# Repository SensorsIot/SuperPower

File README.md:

# SuperPower
Here you should find the best power supplies for your low-power projects. Because of different requirements for an Raspberry Pi and micro-controllers like the ESP32 we split the project into two boards, one for the Raspberry Pi (SuperPower-Rpi) and one for micro-controllers (SuperPower-uC) with low power.

##### [SuperPower-Rpi](/SuperPower-RPi/) for Raspberry Pi

##### [SuperPower-uC](/SuperPower-uC/) for micro-controllers and low-power devices

## Licence

All hardware designs and products you can find in this repository is licensed under [CERN Open Hardware Licence Version 2 - Weakly Reciprocal](/LICENCE.txt)

## Relevant links

[Discord Channel](https://discord.gg/dCr86Hk)  

[Google Drive Project Files](https://drive.google.com/drive/folders/1lCirijHUkISdUYBIRblkILHM6fstifWS)

[GitHub Project](https://github.com/SensorsIot/SuperPower)

[Documentation Website](https://superpower.github.io/)

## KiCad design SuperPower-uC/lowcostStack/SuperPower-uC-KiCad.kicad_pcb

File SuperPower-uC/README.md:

# Super Power uC Project
The Super Power uC Project is the SuperPower for microcontrollers. A ultra low power charging device for
USB and Solar charging for any type of Microcontroller (3.3v). 

# Super Power Variants
## Original Variant
[/SuperPower-uC/original](/SuperPower-uC/original/)

The original version of the SuperPower Board consists of an ESP32 as microcontroller and it tries to fulfill most of the requirements.
We tried to find the best components to fit the requirements with ultra low power. 

[Schematic](/SuperPower-uC/original/schematic.md)

[Layout](/SuperPower-uC/original/layout.md)

### BOM

|      | Component  | Description                                                  | Datasheet                                                    |
| ---- | ---------- | ------------------------------------------------------------ | ------------------------------------------------------------ |
| 1    | LM3671     | 2-MHz, 600-mA Step-Down DC-DC Converter                      | [Link](https://datasheet.lcsc.com/szlcsc/2001161631_Texas-Instruments-LM3671MFX-3-3-NOPB_C477918.pdf) |
| 2    | TPS61032   | 96% Efficient Synchronous Boost Converter With 4A Switch     | [Link](https://www.ti.com/lit/ds/symlink/tps61032.pdf)       |
| 3    | LTC4162-L  | 35V/3.2A Multicell Lithium-Ion Step-Down Battery Charger with PowerPath and I2C Telemetry | [Link](https://www.analog.com/media/en/technical-documentation/data-sheets/LTC4162-L.pdf) |
| 4    | RV-3028-C7 | Extreme Low Power RTC Module 45nA@3V                         | [Link](https://www.microcrystal.com/fileadmin/Media/Products/RTC/Datasheet/RV-3028-C7.pdf) |
| 5    | AP9211     | Single chip protection solution specially designed for 1-cell Li+ | [Link](https://www.diodes.com/assets/Datasheets/AP9211.pdf)  |
| 6    | CP2102N    | highly-integrated USB-to-UART bridge controller              | [Link](https://www.silabs.com/documents/public/data-sheets/cp2102n-datasheet.pdf) |
| 7    | MCP23009   | 8-Bit I2C I/O Expander with Open-Drain Output                | [Link](http://ww1.microchip.com/downloads/en/DeviceDoc/20002121C.pdf) |

## Low Cost Variant

[/SuperPower-uC/lowcost/](/SuperPower-uC/lowcost/)

The low cost variant is a variant with different and cheap components. It does not fulfill the requirements 100% but still is low power.

# How we work

## Branching and Pull-Requests
* The master is the single point of truth and the latest version of the board. Only Merge-Requests are allowed to push changes onto the master.
* each merge-request needs 2 reviewers to be accepted.
* feature branches should start with the term `feature/` and the name of the feature which will be implemented
* try to commit often and atomar and give each commit a nice description of what had been done
* use words like `added`, `fixed`, `changed` etc. at the beginning of your commits

Examples:

`Added Pull up resistor for xyz regulator`

`Changed value of Pull-Up for regulator from 10k to 100k`

`Fixed missing ESP32 Module`

* a git gui tool with timeline view is strongly recommended
* each contributor shall pro actively detect conflicts he creates or created by other branches and get in touch to define a conflict resolution strategy
* key files such as readme and information such as BOM and requirements should be checked by all contributors before merge

## Project phases
* Requirements
* Components selection
* Schematics design
* routing
* testing and validation

## Guidelines for project progress
* Each step of the project progress shall be validated in a group meeting
* After validation, each change in the step (requirements, component) shall be agreed with the Team and not with two reviewers only and PR
* Each feature (mcu / cut_off / charging / low power ...) shall have a maturity level
  * 1 ) clear concept
  * 2 ) design ready
  * 3 ) functional
  * 4 ) stable and bug free
* The maturity level is decided by the Team during a meeting

# Requirements
With the help of a lot participants we collected a list of requirements for this project.

## Filtered Requirements
[Requirements ESP32 Boards shared spreadsheet](https://docs.google.com/spreadsheets/d/1Awvs3CumJ9qQSrG_uEvt4s6nZwliIjnMdfPibDWA3kU/edit#gid=1880015614&fvid=1986096210)

|  | Requirement | Why ? | Discord username | Category | status |
|--|-------------|-------|------------------|----------|--------|
| 1  | Support different ESP modules                         | ESP32 WROOM, WROVER, S2                                                                                                                                                                                                                                                                                                                                          | wassfila       | uC           |  |
| 2  | power cut-off circuit + RTC Timer                     | Cutting off the power lowers the current draw to <1mA                                                                                                                                                                                                                                                                                                            | Informatic0re  | power        |  |
| 4  | 3v3 Output                                            | Power supply for MCU                                                                                                                                                                                                                                                                                                                                             | Andreas Spiess | power        |  |
| 5  | 5V Output                                             | Usefull for sensors which need 5V but should have a on/off                                                                                                                                                                                                                                                                                                       | Andreas Spiess | feature      |  |
| 6  | USB charging                                          |                                                                                                                                                                                                                                                                                                                                                                  | Andreas Spiess | charging     |  |
| 7  | Solar charging                                        | Power for the system when it is installed in locations where USB is not available and where swapping the battery every year or so is not desired                                                                                                                                                                                                                 | Andreas Spiess | charging     |  |
| 8  | Charging while powering                               |                                                                                                                                                                                                                                                                                                                                                                  | Andreas Spiess | charging     |  |
| 9  | Replacable batteries                                  |                                                                                                                                                                                                                                                                                                                                                                  | Andreas Spiess | battery      |  |
| 11 | Low voltage signal/alarm/interrupt                    |                                                                                                                                                                                                                                                                                                                                                                  | Andreas Spiess | power        |  |
| 12 | Battery low voltage protection                        |                                                                                                                                                                                                                                                                                                                                                                  | Andreas Spiess | battery      |  |
| 13 | Over charge and discharge protection                  |                                                                                                                                                                                                                                                                                                                                                                  | Andreas Spiess | battery      |  |
| 14 | charge indicator                                      |                                                                                                                                                                                                                                                                                                                                                                  | Andreas Spiess | charging     |  |
| 25 | Charger control (enable/disable)                      | Reduce the number of charging cycles (specially for solar applications, where we may not want to charge the battery constantly) in order to increase lifespan of battery. AND allow to measure the battery voltage accurately                                                                                                                                    | tealbrains     | charging     |  |
| 26 | Li-Ion Chemistry as 18650, 16340 and FlatPack         | Some users may use Li-Ion 18650 and 16340 or Flat Pack                                                                                                                                                                                                                                                                                                           | tealbrains     | battery      |  |
| 28 | Hysterisis between battery low and battery ready.     | Solar devices in winter may bump along at minimum voltage for extended periods.  For some applications, it may be better for the micro to go to sleep for an extended period to allow the battery to charge more than the minimum amount.                                                                                                                        | metimmee       | feature      |  |
| 32 | Modular architecture with optional components         | Although this might be the main idea already, I added it as requirement to refer to it and translate its impact on the design. This might have to be broken down into what is modular and what not ? RTC optioanl, ESP32 itself optional as mentionned in req_31 ? ...                                                                                           | wassfila       | organisation |  |
| 33 | Test Points                                           | We need test points at any usefull position for proper validating of the circuit                                                                                                                                                                                                                                                                                 | Informatic0re  | feature      |  |
| 34 | Expose ESP32 Serial pinouts for flashing              | If we plan to have a module soldered on the PCB, we would need to flash it, a serial to usb converter might not be necessary to be on the pcb as it could be similar to the ESP32-cam with external serial to usb. Use https://randomnerdtutorials.com/esp32-pinout-reference-gpios/ as aa reference (very good) And do not expose GPIO36! Ask Informatic0re why | wassfila       | uC           |  |
| 35 | LOW power consumption (of the regulator board itself) | In Solar powered applications, the overhead power consumtion of chargers/regulators can be too much.                                                                                                                                                                                                                                                             |                |              |  |
| 37 | Usb C                                                 | This will make it more future-proof and its going to be nice to have the new usb standard while not having to worry about wich way you connect the usb                                                                                                                                                                                                           | fabrifer020    | feature      |  |
| 38 | Reverse voltage protection                            | To not fry our Boards with a common mistake that could be prevented with just a few components and negligible current loss for saving our boards                                                                                                                                                                                                                 | fabrifer020    | safety       |  |
| 40 | Controllable 3v3 Output                               | A 3.3V Output which can be tunred on and off by the MCU to power sensors and other things                                                                                                                                                                                                                                                                        | leven          |              |  |
| 43 | Expose Battery pins (post protection)                 | This allows the user to power some modems or loads directly from the battery without extra losses that occur using a voltage regulator                                                                                                                                                                                                                           | tealbrains     | feature      |  |
| 46 | Having Both Holder And Connecter                      | Having both 18650 Holder and connector terminals for li-po battery would provide grea flexibility                                                                                                                                                                                                                                                                | Trance_Paradox | feature      |  |
| 50 | Short Circuit Protection on the output                | we all know why...... :D                                                                                                                                                                                                                                                                                                                                         | johnheuk       | safety       |  |
| 53 | Barrel Jack / Screw Terminals                         | not everyone has a soldering iron, or one that's good enough to solder to via stitched ground planes, or may not have a spare usb lead. having a few different connection methods would be great                                                                                                                                                                 | johnheuk       | feature      |  |
| 63 | Expose unused ESP32 GPIO Pins                         | The reference board in the video shows gpio exposed on a header on the sides, and it makes sense that a maker that needs this PCB also wants to use the ESP32 gpios he paid for.                                                                                                                                                                                 | wassfila       | uC           |  |
| 88 | Open Hardware License                                 | We might need to choose a license to open source our hardware properly                                                                                                                                                                                                                                                                                           | Noki           |              |  |

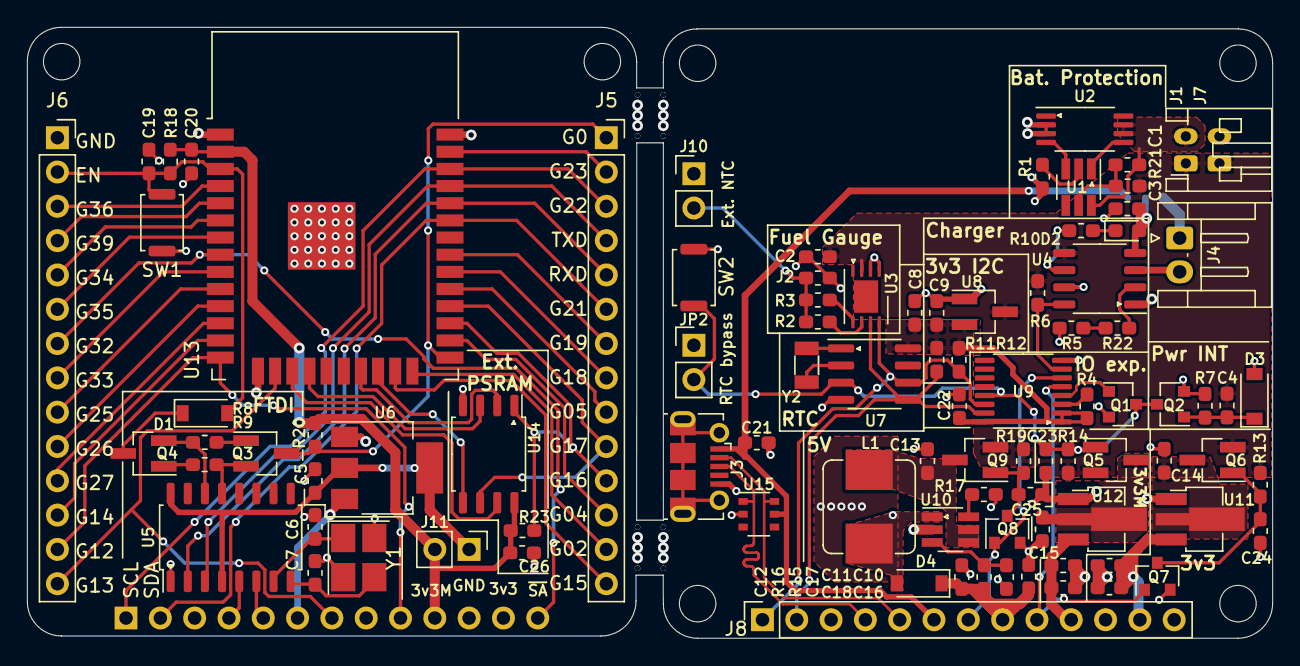
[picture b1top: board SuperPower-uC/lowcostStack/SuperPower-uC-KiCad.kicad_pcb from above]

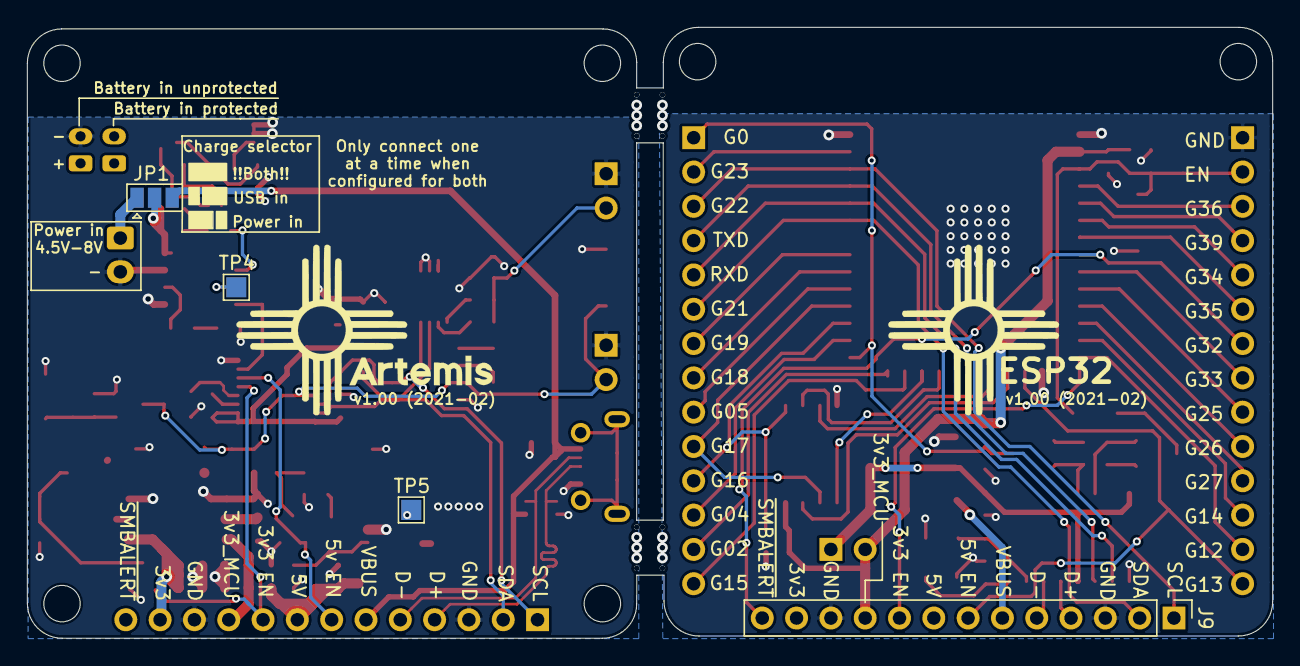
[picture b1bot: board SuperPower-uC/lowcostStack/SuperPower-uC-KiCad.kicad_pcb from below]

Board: 4 copper layers, 92.2 x 45.2 mm, 103 parts (4 on the bottom side), 86 nets.

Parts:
C1, C2, C8, C9, C14, C15, C20, C23, C24, C25, C26: 0.1µF; C_0603_1608Metric_Pad1.05x0.95mm_HandSolder
C3, C4, C5, C10, C11, C12, C13, C19, C21, C22: 1µF; C_0603_1608Metric_Pad1.05x0.95mm_HandSolder
C6, C7: 22pF; C_0603_1608Metric_Pad1.05x0.95mm_HandSolder
C16, C17, C18: 10µF; C_0603_1608Metric_Pad1.05x0.95mm_HandSolder
D1, D3, D4: B5819W; D_SOD-123
D2: LED; LED_0603_1608Metric_Pad1.05x0.95mm_HandSolder
H1, H2, H3, H4, H5, H6: MountingHole; MountingHole_2.7mm_M2.5_ISO7380
J1: Battery connector; JST_PH_S2B-PH-K_1x02_P2.00mm_Horizontal
J2: Thermistor; R_0603_1608Metric_Pad1.05x0.95mm_HandSolder
J3: USB_B_Micro; USB_Micro-B_Molex-105017-0001
J4: Solar in; JST_EH_S2B-EH_1x02_P2.50mm_Horizontal
J5, J6: Conn_01x14_Female; PinSocket_1x14_P2.54mm_Vertical
J7: DNP; JST_PH_S2B-PH-K_1x02_P2.00mm_Horizontal
J8: regulator board; PinSocket_1x13_P2.54mm_Vertical
J9: MCU board; PinHeader_1x13_P2.54mm_Vertical
J10: External NTC; PinHeader_1x02_P2.54mm_Vertical
J11: DNP; PinHeader_1x02_P2.54mm_Vertical
JP1: CHRG_Jumper; SolderJumper-3_P1.3mm_Open_Pad1.0x1.5mm
JP2: RTC bypass; PinHeader_1x02_P2.54mm_Vertical
L1: 3.3u; L_Bourns_SRP7028A_7.3x6.6mm
Q1, Q2, Q7, Q8: 2N7002; SOT-23
Q3, Q4: S8050; SOT-23_Handsoldering
Q5, Q6, Q9: AO3401A; SOT-23_Handsoldering
R1, R5, R10, R22: 1k; R_0603_1608Metric_Pad1.05x0.95mm_HandSolder
R2: 100; R_0603_1608Metric_Pad1.05x0.95mm_HandSolder
R3, R8, R9, R11, R12, R18, R20, R23: 10k; R_0603_1608Metric_Pad1.05x0.95mm_HandSolder
R4, R6, R16: 180k; R_0603_1608Metric_Pad1.05x0.95mm_HandSolder
R7, R13, R14, R19: 1M; R_0603_1608Metric_Pad1.05x0.95mm_HandSolder
R15, R17: 22k; R_0603_1608Metric_Pad1.05x0.95mm_HandSolder
R21: 330; R_0603_1608Metric_Pad1.05x0.95mm_HandSolder
SW1, SW2: DNP; SW_Push_SPST_NO_Alps_SKRK
TP4, TP5: TestPoint; TestPoint_Pad_1.5x1.5mm
U1: AP9101CK6-ADTRG1; SOT-23-6_Handsoldering
U2: FS8205A; TSSOP-8_4.4x3mm_P0.65mm
U3: LC709203FQH; WDFN-8-1EP_4x3mm_P0.65mm_EP2.4x1.8mm
U4: TP4056; SOP-8_3.9x4.9mm_P1.27mm
U5: CH340G; SOP-16_4.55x10.3mm_P1.27mm
U6: AMS1117-3.3; SOT-223-3_TabPin2
U7: PCF8563T; SOIC-8_3.9x4.9mm_P1.27mm
U8: XC6206P332MR; SOT-23_Handsoldering
U9: TCA6408A; TSSOP-16_4.4x5mm_P0.65mm
U10: FP6291LR; SOT-23-6_Handsoldering
U11, U12: ME6210A33P; SOT-89-3_Handsoldering
U13: ESP32-WROOM32; ESP32-WROOM-32
U14: W25Q32JVSS; SOIC-8_5.23x5.23mm_P1.27mm
U15: IP4220CZ6; TSOP-6_1.65x3.05mm_P0.95mm
Y1: 12MHZ; Crystal_SMD_3225-4Pin_3.2x2.5mm_HandSoldering
Y2: 32.768KHz; Crystal_SMD_3215-2Pin_3.2x1.5mm

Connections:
3v3_EN: J8.9, Q7.1, U9.5
5V_EN: J8.7, Q8.1, U9.6
/3v3: C10.1, C16.1, J8.12, U11.3
/3v3_MCU_1: C11.1, C18.1, J8.10, U12.3
/3v3_MCU_2: C20.2, C26.2, J9.10, J11.2, R18.1, R20.1, R23.1, U13.2, U14.8
/5v: C12.1, C17.1, D4.1, J8.8, R16.1
/Battery Module/BAT-: C1.2, J1.2, U1.6, U2.6, U2.7
/Battery Module/VBAT: C2.2, C4.1, J1.1, J7.1, Q5.2, Q6.2, Q9.2, R6.1, R13.2, R14.2, R19.2, R21.1, U3.3, U4.5, U8.3
/Charger I/O/VCHARGE: C3.1, D2.2, JP1.2, U4.4
/Charging Module/3v3_I2C: C8.2, C9.2, C22.2, R4.1, R11.2, R12.2, U7.8, U8.2, U9.1, U9.2, U9.16
/Charging Module/STDBY: R10.2, U4.6
/D1+: J3.3, J8.4, U15.1
/D1-: J3.2, J8.5, U15.6
/D2+: J9.4, U5.5
/D2-: J9.5, U5.6
/EN_3v3: J6.13, J9.9, U13.14
/EN_5v: J6.14, J9.7, U13.16
/MCU Module/3v3FTDI: C5.2, J11.1, U5.4, U5.16, U6.2
/MCU Module/IO0: J5.1, Q3.3, R20.2, U13.25
/MCU Module/IO2: J5.13, U13.24
/MCU Module/IO4: J5.12, U13.26
/MCU Module/IO5: J5.9, U13.29
/MCU Module/IO14: J6.12, U13.13
/MCU Module/IO15: J5.14, U13.23
/MCU Module/IO16: J5.11, R23.2, U13.27, U14.1
/MCU Module/IO17: J5.10, U13.28, U14.6
/MCU Module/IO18: J5.8, U13.30
/MCU Module/IO19: J5.7, U13.31
/MCU Module/IO23: J5.2, U13.37
/MCU Module/IO25: J6.9, U13.10
/MCU Module/IO26: J6.10, U13.11
/MCU Module/IO27: J6.11, U13.12
/MCU Module/IO33: J6.8, U13.9
/MCU Module/IO34: J6.5, U13.6
/MCU Module/IO35: J6.6, U13.7
/MCU Module/IO36: J6.3, U13.4
/MCU Module/IO39: J6.4, U13.5
/MCU Module/PSRAM_SD0: U13.21, U14.2
/MCU Module/PSRAM_SD1: U13.22, U14.5
/MCU Module/PSRAM_SD2: U13.17, U14.7
/MCU Module/PSRAM_SD3: U13.18, U14.3
/MCU Module/RST: C19.1, D1.2, J6.2, R18.2, SW1.1, U13.3
/MCU Module/RX: J5.5, U5.2, U13.34
/MCU Module/TX: J5.4, U5.3, U13.35
/SCL_1: J8.1, R12.1, U3.8, U7.6, U9.14
/SCL_2: J5.3, J9.1, U13.36
/SDA_1: J8.2, R11.1, U3.7, U7.5, U9.15
/SDA_2: J5.6, J9.2, U13.33
/VBUS_1: C21.1, J3.1, J8.6, JP1.3, U15.5
/VBUS_2: J9.6, U6.3
/~SMBALERT: J6.7, J9.13, U13.8
CH_DIS: R6.2, U4.8, U9.7
GND: C2.1, C3.2, C5.1, C6.2, C7.2, C8.1, C9.1, C10.2, C11.2, C12.2, C13.2, C14.2, C15.2, C16.2, C17.2, C18.2, C19.2, C20.1, C21.2, C22.1, C23.1, C24.2, C25.2, C26.1, D3.2, J2.2, J3.5, J4.2, J6.1, J7.2, J8.3, J8.11, J9.3, J9.11, J10.1, JP2.1, Q1.2, Q2.2, Q7.2, Q8.2, R1.2, R5.2, R7.1, R15.2, R17.2, SW1.2, SW2.2, U2.2, U2.3, U3.1, U3.2, U4.1, U4.3, U5.1, U6.1, U7.4, U8.1, U9.8, U10.2, U11.1, U12.1, U13.1, U13.15, U13.38, U13.39, U14.4, U15.2, Y1.2, Y1.4
INT_IO: C23.2, JP2.2, Q1.3, Q2.3, Q5.1, R14.1, SW2.1, U7.3, U9.13
unnamed: C1.1, R21.2, U1.5
unnamed: C4.2, D3.1, Q2.1, R7.2
unnamed: C6.1, U5.7, Y1.1
unnamed: C7.1, U5.8, Y1.3
unnamed: C13.1, L1.1, Q9.3, U10.4, U10.5
unnamed: C14.1, Q6.3, U11.2
unnamed: C15.1, Q5.3, U12.2
unnamed: C24.1, Q6.1, Q7.3, R13.1
unnamed: C25.1, Q8.3, Q9.1, R19.1
unnamed: D1.1, Q4.3
unnamed: D2.1, R10.1
unnamed: D4.2, L1.2, TP5.1, U10.1
unnamed: J4.1, JP1.1
unnamed: J2.1, J10.2, R2.2, R3.2
unnamed: Q1.1, U9.4
unnamed: Q3.1, R8.1
unnamed: Q3.2, R9.2, U5.13
unnamed: Q4.1, R9.1
unnamed: Q4.2, R8.2, U5.14
unnamed: R1.1, U1.2
unnamed: R2.1, U3.6
unnamed: R3.1, U3.5
unnamed: R4.2, U9.3
unnamed: R15.1, R16.2, U10.3
unnamed: R17.1, U10.6
unnamed: R22.1, U4.2
unnamed: R5.1, R22.2
unnamed: TP4.1, U4.7
unnamed: U1.1, U2.5
unnamed: U1.3, U2.4
unnamed: U7.1, Y2.2
unnamed: U7.2, Y2.1

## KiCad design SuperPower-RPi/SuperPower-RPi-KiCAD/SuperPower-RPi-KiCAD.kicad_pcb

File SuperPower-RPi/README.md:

# Super Power RPi Project

[Documentation](https://superpower.readthedocs.io/en/latest/rpi/overview.html)

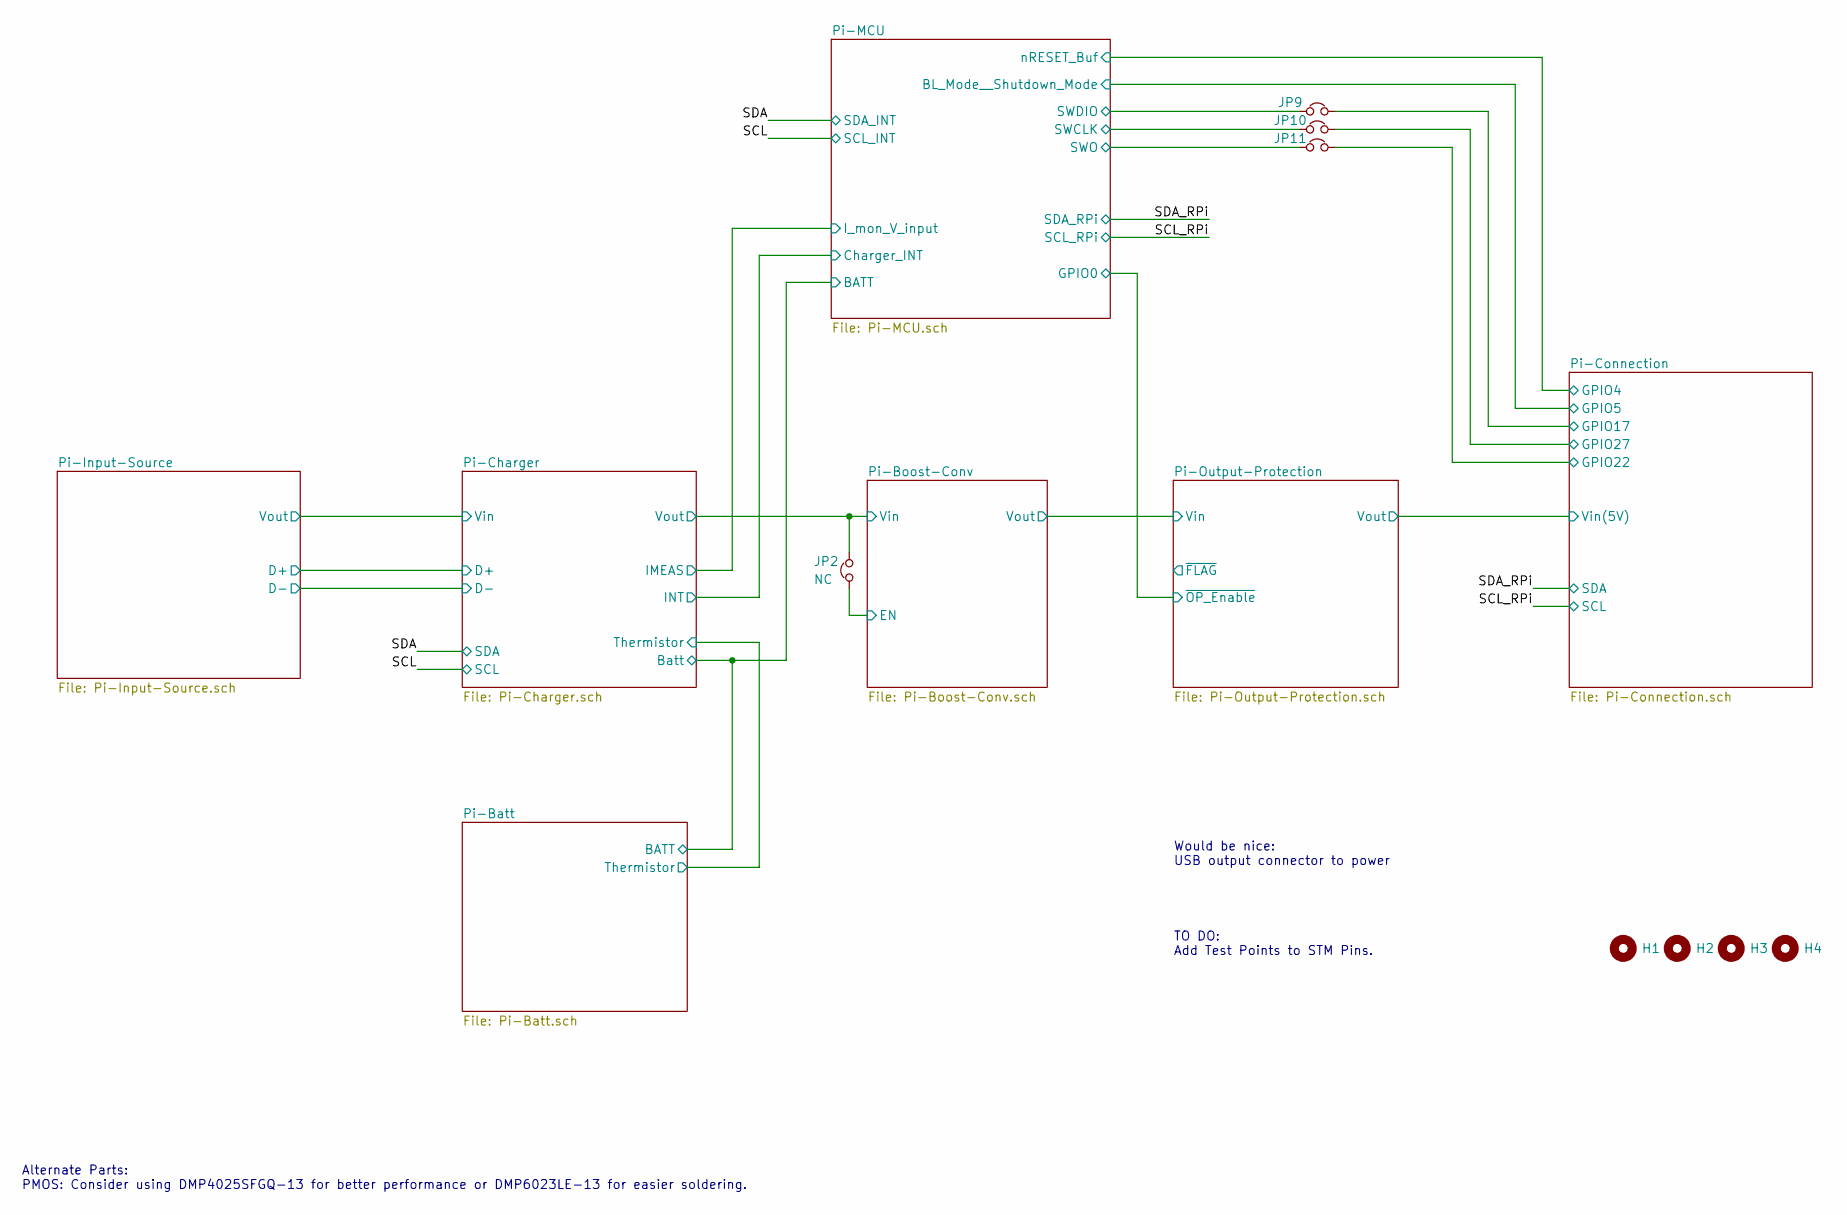
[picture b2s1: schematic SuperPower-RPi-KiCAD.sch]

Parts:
H1, H2, H3, H4: DNP; MountingHole_2.7mm_M2.5_ISO14580_Pad_TopBottom
JP2: NC; SolderJumper-2_P1.3mm_Bridged_Pad1.0x1.5mm
JP9, JP10, JP11: Jumper_NC_Small; SolderJumper-2_P1.3mm_Bridged_Pad1.0x1.5mm

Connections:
/Pi-Boost-Conv/EN: JP2.1; also elsewhere on the board
/Pi-Boost-Conv/Vin: JP2.2; also elsewhere on the board
/Pi-Connection/GPIO17: JP9.2; also elsewhere on the board
/Pi-Connection/GPIO22: JP11.2; also elsewhere on the board
/Pi-Connection/GPIO27: JP10.2; also elsewhere on the board
/Pi-MCU/SWCLK: JP10.1; also elsewhere on the board
/Pi-MCU/SWDIO: JP9.1; also elsewhere on the board
/Pi-MCU/SWO: JP11.1; also elsewhere on the board

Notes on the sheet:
Alternate Parts: PMOS: Consider using DMP4025SFGQ-13 for better performance or DMP6023LE-13 for easier soldering.
TO DO: Add Test Points to STM Pins.
Would be nice: USB output connector to power

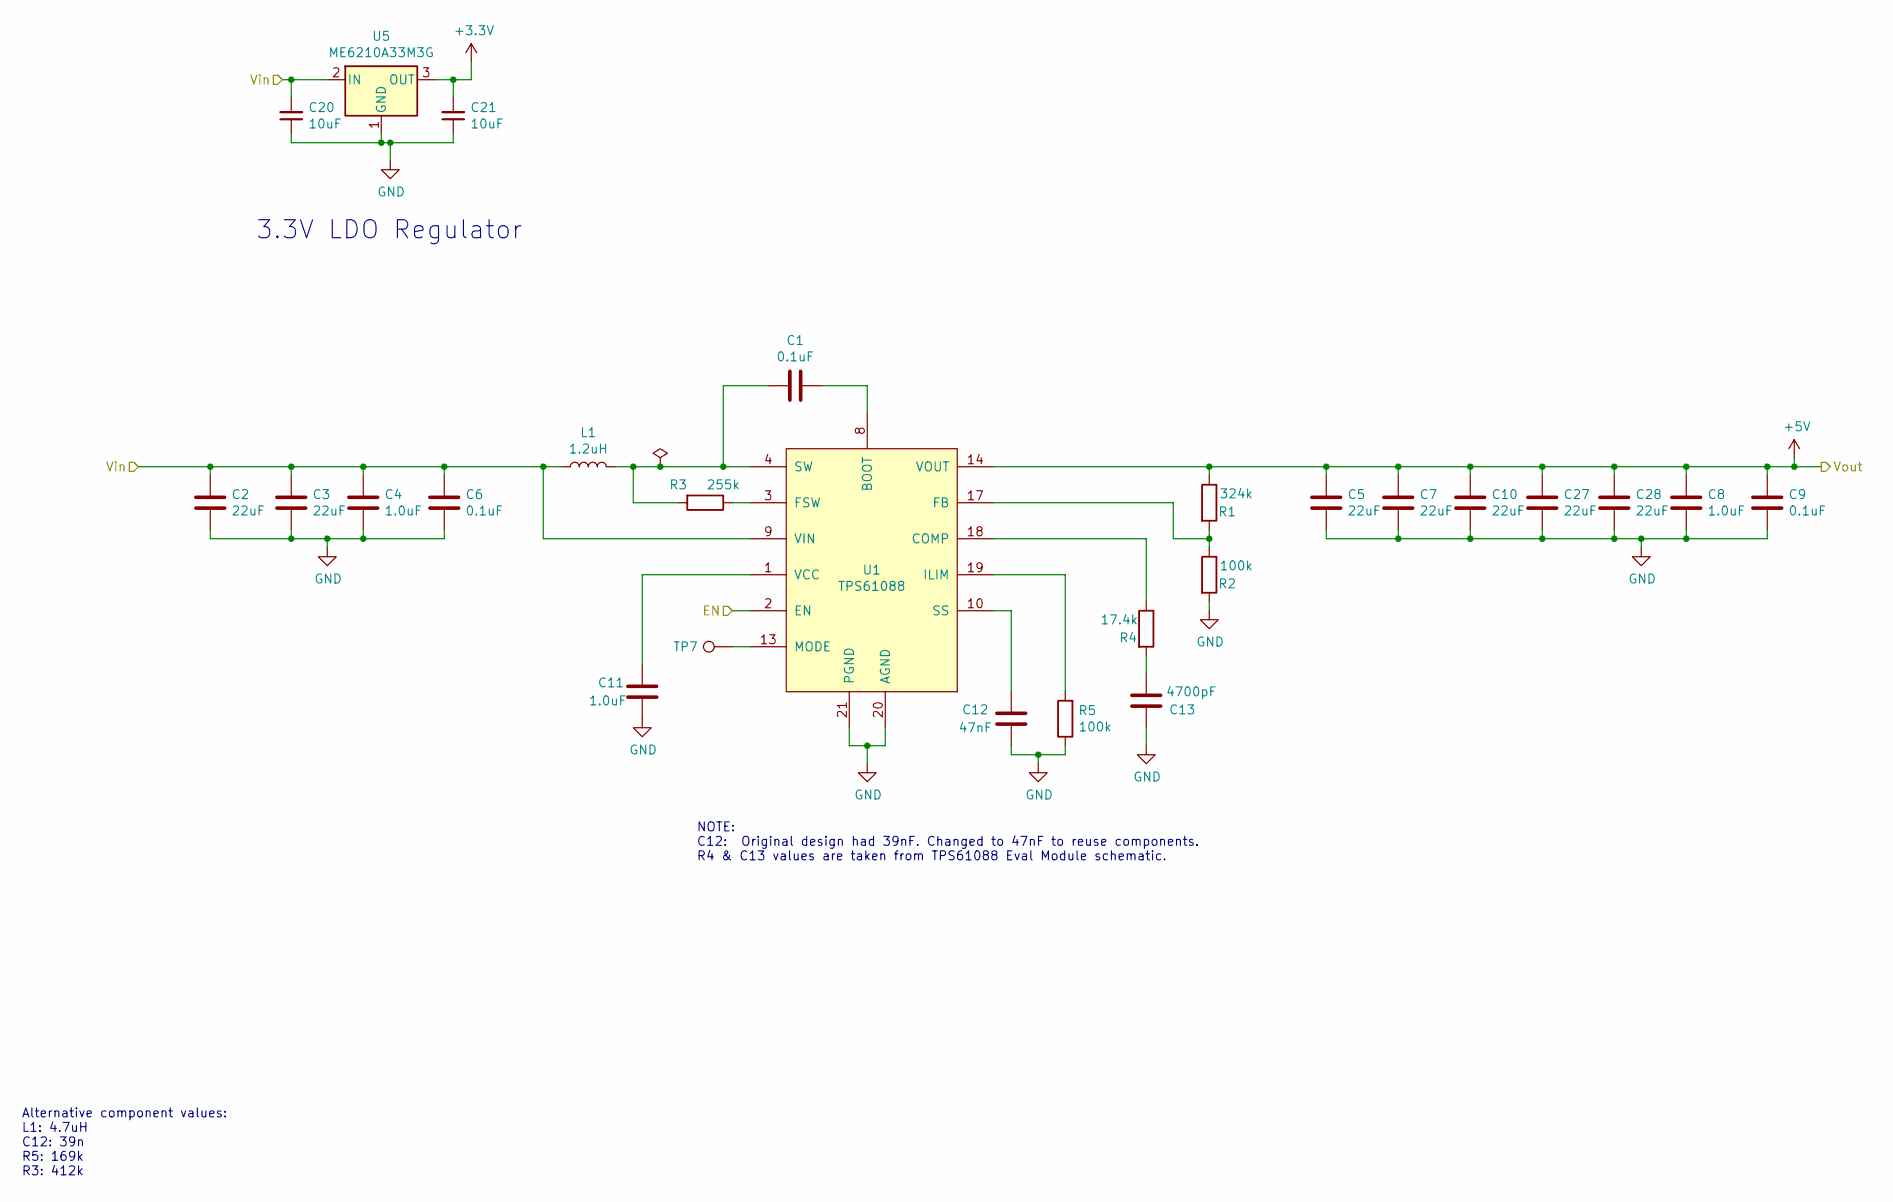
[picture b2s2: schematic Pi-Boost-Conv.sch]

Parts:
C1, C6, C9: 0.1uF; C_0402_1005Metric; Mfg PN TMK105BJ104KV-F; Digi-Key PN 587-1456-1-ND
C2, C3, C5, C7, C10, C27, C28: 22uF; C_1206_3216Metric; Mfg PN CL31A226KAHNNNE; Digi-Key PN 1276-3047-1-ND
C4, C8, C11: 1.0uF; C_0402_1005Metric; Mfg PN GRM155R61E105KA12D; Digi-Key PN 490-10017-1-ND
C12: 47nF; C_0402_1005Metric; Mfg PN GRM155R71E473KA88D; Digi-Key PN 490-3254-1-ND
C13: 4700pF; C_0402_1005Metric; Mfg PN CC0402KRX7R8BB472; Digi-Key PN 311-1039-1-ND
C20, C21: 10uF; C_0805_2012Metric; Mfg PN GRM21BR61E106KA73L; Digi-Key PN 490-5523-1-ND
L1: 1.2uH; L_Sumida_CDMC8D28_9.5x8.7mm; Mfg PN CDMC8D28NP-1R2MC; Digi-Key PN 308-1618-1-ND
R1: 324k; R_0402_1005Metric; Mfg PN ERJ-2RKF3243X; Digi-Key PN P324KLCT-ND
R2: 100k; R_0402_1005Metric; Mfg PN RC0402FR-07100KL; Digi-Key PN 311-100KLRCT-ND
R3: 255k; R_0603_1608Metric; Mfg PN RC0603FR-07255KL; Digi-Key PN 311-255KHRCT-ND
R4: 17.4k; R_0402_1005Metric; Mfg PN RC0402FR-0717K4L; Digi-Key PN 311-17.4KLRCT-ND
R5: 100k; R_0603_1608Metric; Mfg PN RC0603FR-07100KL; Digi-Key PN 311-100KHRCT-ND
TP7: DNP; TestPoint_Pad_1.0x1.0mm
U1: TPS61088; TI_VQFN_3.5x4.5mm; Mfg PN TPS61088RHLR; Digi-Key PN 296-43620-1-ND
U5: ME6210A33M3G; SOT-23; Mfg PN ME6210A33M3G

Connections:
+3V3: C21.2, U5.3 (OUT); also elsewhere on the board
+5V: C5.1, C7.1, C8.1, C9.1, C10.1, C27.1, C28.1, R1.1, U1.14 (VOUT), U1.15 (VOUT), U1.16 (VOUT); also elsewhere on the board
/Pi-Boost-Conv/EN: U1.2 (EN); also elsewhere on the board
/Pi-Boost-Conv/Vin: C2.1, C3.1, C4.1, C6.1, C20.2, L1.1, U1.9 (VIN), U5.2 (IN); also elsewhere on the board
GND: C2.2, C3.2, C4.2, C5.2, C6.2, C7.2, C8.2, C9.2, C10.2, C11.2, C12.1, C13.2, C20.1, C21.1, C27.2, C28.2, R2.2, R5.1, U1.11 (NC), U1.12 (NC), U1.20 (AGND), U1.21 (PGND), U5.1 (GND); also elsewhere on the board
unnamed: C1.1, U1.8 (BOOT)
unnamed: C1.2, L1.2, R3.2, U1.4 (SW), U1.5 (SW), U1.6 (SW), U1.7 (SW)
unnamed: C11.1, U1.1 (VCC)
unnamed: C12.2, U1.10 (SS)
unnamed: C13.1, R4.2
unnamed: R1.2, R2.1, U1.17 (FB)
unnamed: R3.1, U1.3 (FSW)
unnamed: R4.1, U1.18 (COMP)
unnamed: R5.2, U1.19 (ILIM)
unnamed: TP7.1, U1.13 (MODE)

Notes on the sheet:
Alternative component values: L1: 4.7uH C12: 39n R5: 169k R3: 412k
3.3V LDO Regulator
NOTE: C12: Original design had 39nF. Changed to 47nF to reuse components. R4 & C13 values are taken from TPS61088 Eval Module schematic.

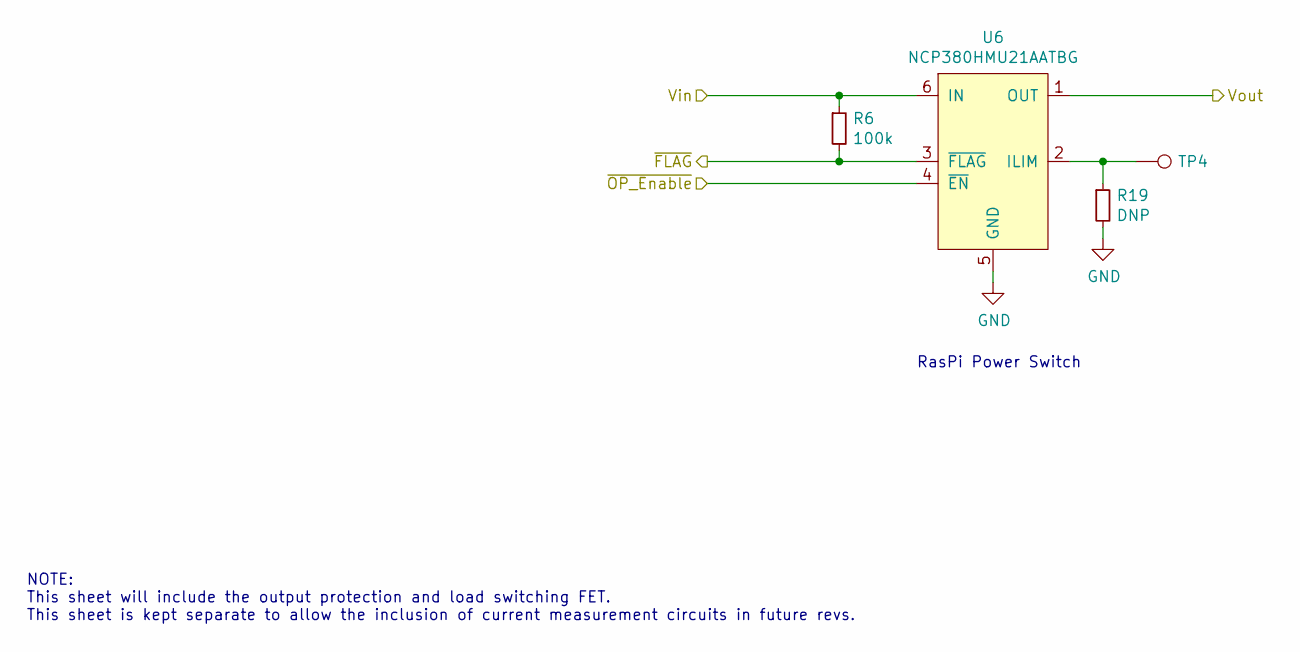
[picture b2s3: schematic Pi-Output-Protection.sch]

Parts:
R6: 100k; R_0402_1005Metric; Mfg PN RC0402FR-07100KL; Digi-Key PN 311-100KLRCT-ND
R19: DNP; R_0603_1608Metric; Mfg PN DNP; Digi-Key PN DNP
TP4: DNP; TestPoint_Pad_1.0x1.0mm
U6: NCP380HMU21AATBG; UDFN-6-1EP_2x2mm_P0.65mm_EP0.95x1.7mm; Mfg PN NCP380HMU21AATBG; Digi-Key PN NCP380HMU21AATBGOSCT-ND

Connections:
+5V: R6.1, U6.6 (IN); also elsewhere on the board
/Pi-Connection/Vin(5V): U6.1 (OUT); also elsewhere on the board
/Pi-MCU/GPIO0: U6.4 (~EN); also elsewhere on the board
/Pi-Output-Protection/~FLAG: R6.2, U6.3 (~FLAG)
GND: R19.2, U6.5 (GND), U6.7 (PAD); also elsewhere on the board
unnamed: R19.1, TP4.1, U6.2 (ILIM)

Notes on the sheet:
NOTE: This sheet will include the output protection and load switching FET. This sheet is kept separate to allow the inclusion of current measurement circuits in future revs.
RasPi Power Switch

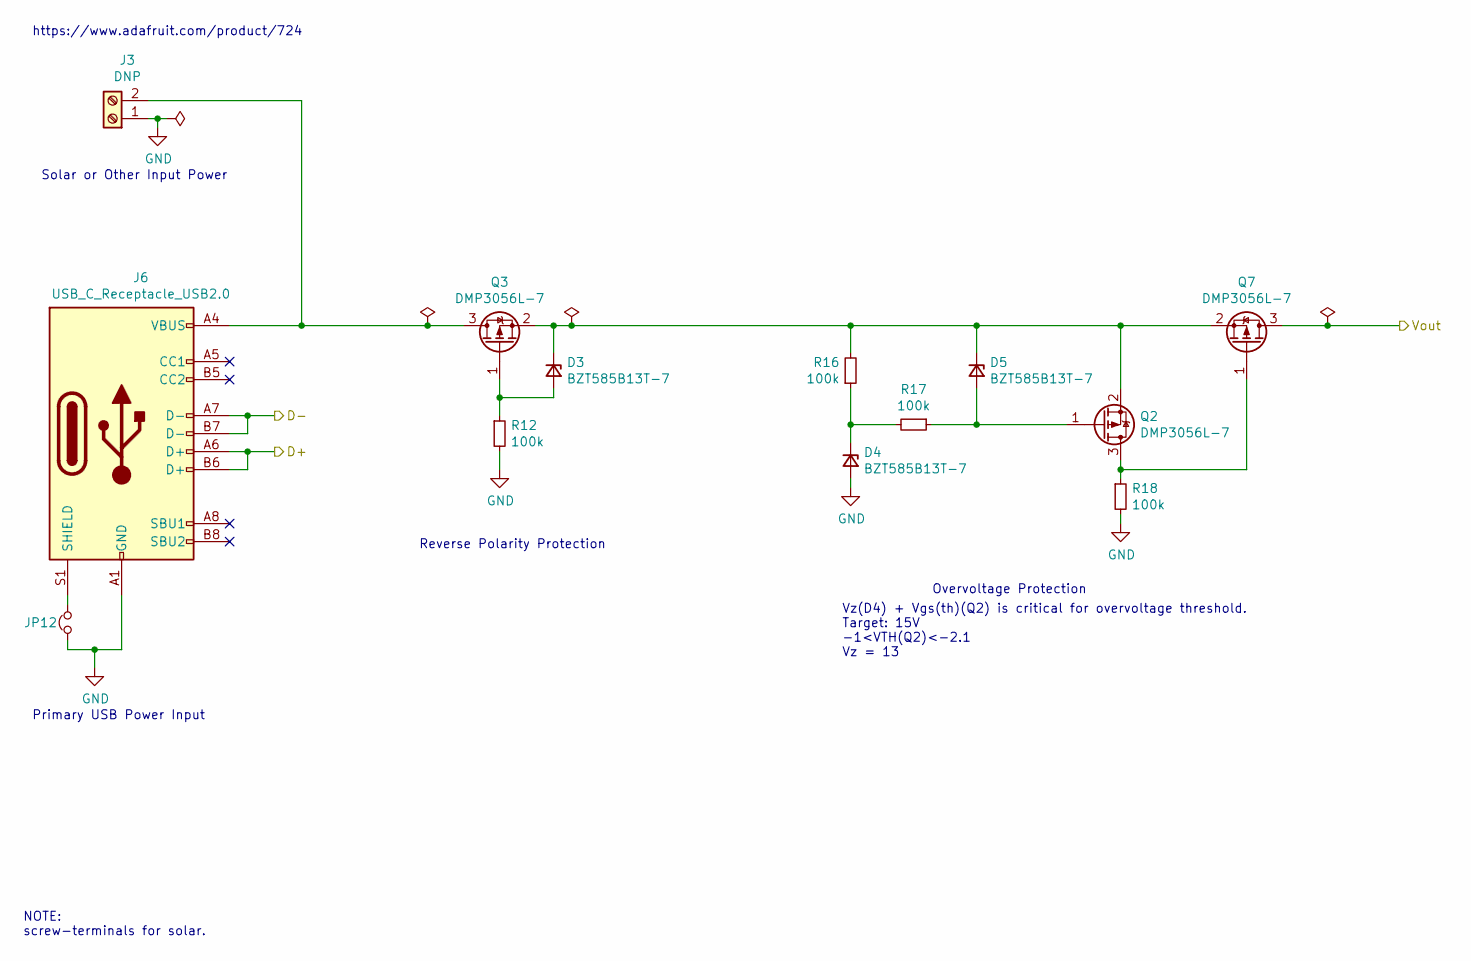
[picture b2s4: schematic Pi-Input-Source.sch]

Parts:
D3, D4, D5: BZT585B13T-7; D_SOD-523; Mfg PN BZT585B13T-7; Digi-Key PN BZT585B13T-7DICT-ND
J3: DNP; TerminalBlock_4Ucon_1x02_P3.50mm_Horizontal; Mfg PN 724
J6: USB_C_Receptacle_USB2.0; USB_C_Receptacle_HRO_TYPE-C-31-M-12; Mfg PN TYPE-C-31-M-12
JP12: Jumper_NC_Small; SolderJumper-2_P1.3mm_Bridged_Pad1.0x1.5mm
Q2, Q3, Q7: Q_PMOS_DMP3056L-7_SOT-23; SOT-23; Mfg PN DMP3056L-7; Digi-Key PN DMP3056L-7DICT-ND
R12, R16, R17, R18: 100k; R_0402_1005Metric; Mfg PN RC0402FR-07100KL; Digi-Key PN 311-100KLRCT-ND

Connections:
/Pi-Charger/D+: J6.A6 (D+), J6.B6 (D+); also elsewhere on the board
/Pi-Charger/D-: J6.A7 (D-), J6.B7 (D-); also elsewhere on the board
/Pi-Charger/Vin: Q7.3 (D); also elsewhere on the board
GND: D4.2 (A), J3.1, J6.A1 (GND), J6.A12 (GND), J6.B1 (GND), J6.B12 (GND), JP12.1, R12.2, R18.2; also elsewhere on the board
unnamed: D3.1 (K), D5.1 (K), Q2.2 (S), Q3.2 (S), Q7.2 (S), R16.2
unnamed: D3.2 (A), Q3.1 (G), R12.1
unnamed: D4.1 (K), R16.1, R17.2
unnamed: D5.2 (A), Q2.1 (G), R17.1
unnamed: J3.2, J6.A4 (VBUS), J6.A9 (VBUS), J6.B4 (VBUS), J6.B9 (VBUS), Q3.3 (D)
unnamed: J6.S1 (SHIELD), JP12.2
unnamed: Q2.3 (D), Q7.1 (G), R18.1

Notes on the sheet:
Solar or Other Input Power
NOTE: screw-terminals for solar.
Reverse Polarity Protection
Overvoltage Protection
Vz(D4) + Vgs(th)(Q2) is critical for overvoltage threshold. Target: 15V -1<VTH(Q2)<-2.1 Vz = 13
https://www.adafruit.com/product/724
Primary USB Power Input

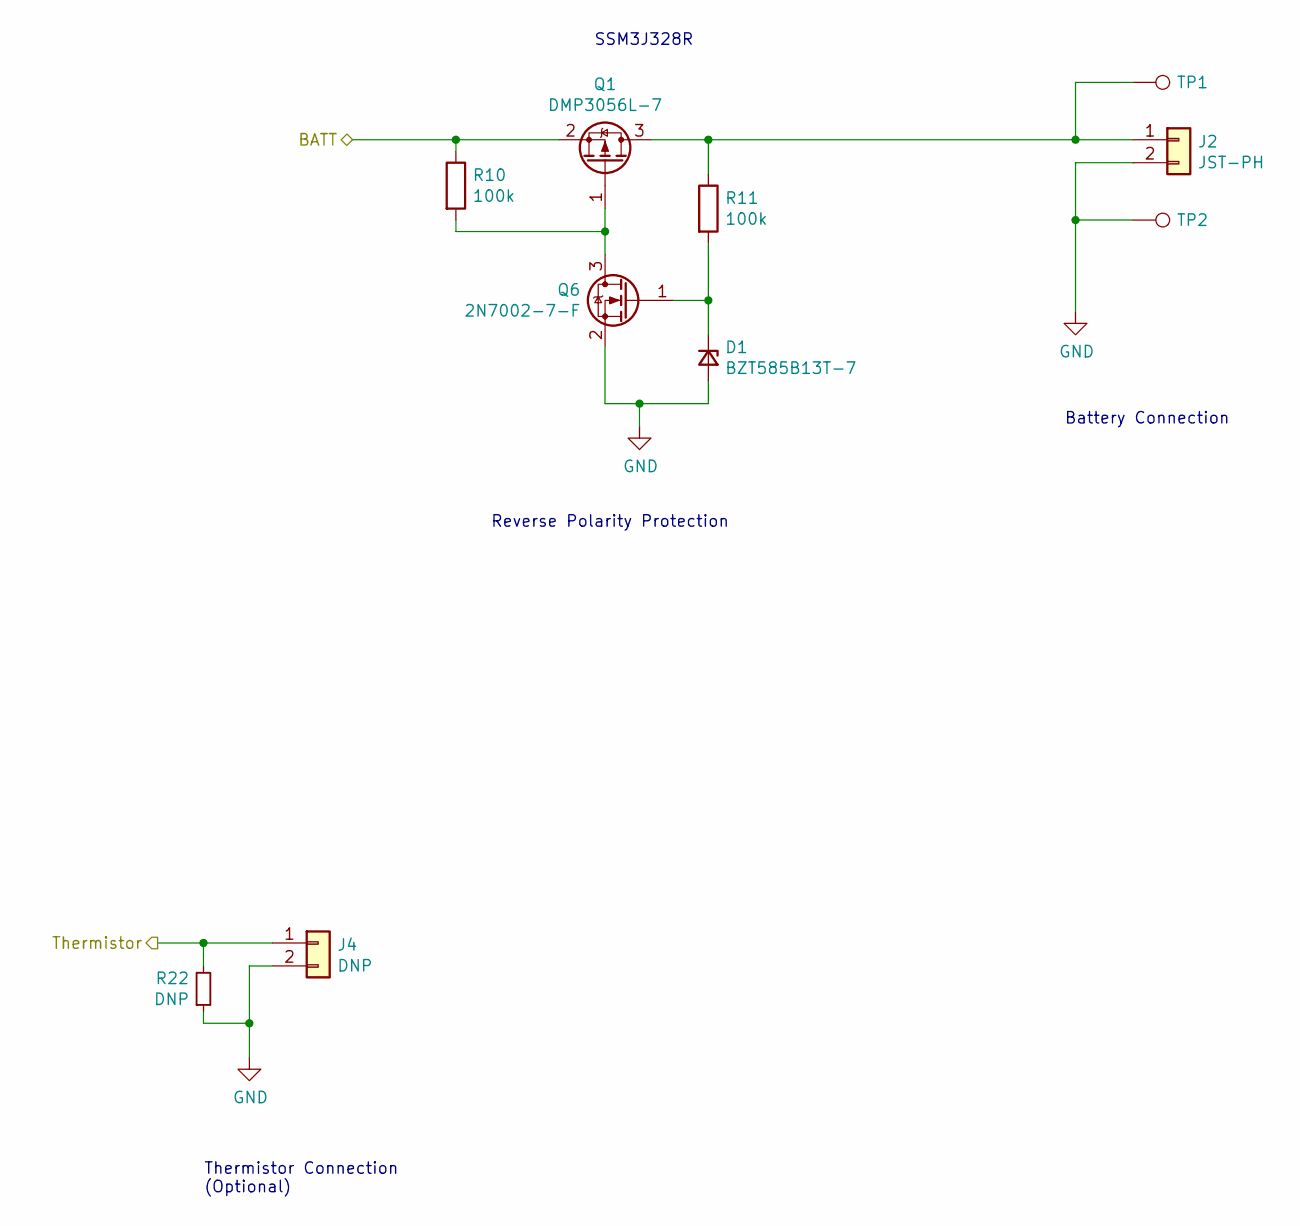
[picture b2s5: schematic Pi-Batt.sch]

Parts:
D1: BZT585B13T-7; D_SOD-523; Mfg PN BZT585B13T-7; Digi-Key PN BZT585B13T-7DICT-ND
J2: JST-PH; JST_PH_S2B-PH-K_1x02_P2.00mm_Horizontal; Mfg PN S2B-PH-K-S(LF)(SN)
J4: DNP; PinHeader_1x02_P2.00mm_Vertical; Mfg PN DNP
Q1: Q_PMOS_DMP3056L-7_SOT-23; SOT-23; Mfg PN DMP3056L-7; Digi-Key PN DMP3056L-7DICT-ND
Q6: 2N7002-7-F; SOT-23; Mfg PN 2N7002-7-F; Digi-Key PN 2N7002-FDICT-ND
R10, R11: 100k; R_0402_1005Metric; Mfg PN RC0402FR-07100KL; Digi-Key PN 311-100KLRCT-ND
R22: DNP; R_0603_1608Metric
TP1, TP2: DNP; SolderWire-1.5sqmm_1x01_D1.7mm_OD3.9mm

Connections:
/Pi-Batt/BATT: Q1.2 (S), R10.1; also elsewhere on the board
/Pi-Batt/Thermistor: J4.1, R22.2; also elsewhere on the board
GND: D1.2 (A), J2.2, J4.2, Q6.2 (S), R22.1, TP2.1; also elsewhere on the board
unnamed: D1.1 (K), Q6.1 (G), R11.2
unnamed: J2.1, Q1.3 (D), R11.1, TP1.1
unnamed: Q1.1 (G), Q6.3 (D), R10.2

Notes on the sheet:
Reverse Polarity Protection
Thermistor Connection (Optional)
Battery Connection
SSM3J328R
